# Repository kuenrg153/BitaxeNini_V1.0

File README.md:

# Bitaxe Nini V2.0

Bitaxe Nini is an open-source Bitcoin miner board with **four KF1950 ASICs**. It is a derivative of the
[Bitaxe Gamma Turbo (BitaxeGT)](https://github.com/bitaxeorg/BitaxeGT) and is designed in KiCad 10.

## Features

- 4 x KF1950 ASICs on the bottom side, cooled by a ridged 68 x 68 mm heatsink
- TPS546D24S buck regulator for the ASIC core supply
- ESP32-S3-WROOM-1 controller with USB-C
- 12 V input (screw terminal J1, with an alternate J9 position)
- EMC2101 and EMC2103-2 fan control and temperature monitoring
- 0.91" 128 x 32 I2C OLED module (J4)
- Top-side heat spreading: exposed copper pours and filled thermal vias under a 60 x 44 x 44 mm finned heatsink
  (mounted on electrically insulating thermal tape), plus a 12 x 12 x 5 mm heatsink on the regulator
- 65.1 x 112.1 mm, 4-layer, 2 oz outer copper, ENIG, filled and capped via-in-pad

Firmware: [kuenrg153/ESP-Miner](https://github.com/kuenrg153/ESP-Miner), the ESP-Miner fork for the KF1950.

## Repository layout

| Path | Contents |
|---|---|
| `BitaxeNini_V2.0.kicad_pro` / `.kicad_sch` / `.kicad_pcb` | KiCad project, schematics (ASIC, Power, ESP32, fan sheets) and board |
| `bitaxe.kicad_sym`, `bitaxe.pretty/`, `3d/` | Project library: symbols, footprints and 3D models (bundled, no external library needed) |
| `Manufacturing Files/` | Gerbers, drill files, BOM with DigiKey part numbers, pick-and-place, fab and assembly drawings, `FAB_NOTES.txt` |
| `BitaxeNini_V2.0.step` | Full 3D assembly model |
| `doc/` | Renders |

The project library is referenced through `${KIPRJMOD}`, so the project opens with all footprints and 3D models
straight after cloning.

## Manufacturing

Upload `Manufacturing Files/BitaxeNini_V2.0_MFG_261119.zip` to the board house and include the notes in
`Manufacturing Files/FAB_NOTES.txt`. Key requirements: via-in-pad filled and capped (IPC-4761 Type VII) and the
intentional front solder-mask openings. The KF1950 ASICs are not sold by distributors and are supplied separately.

## License

This project is licensed under the
[CERN Open Hardware Licence Version 2 - Strongly Reciprocal (CERN-OHL-S-2.0)](https://choosealicense.com/licenses/cern-ohl-s-2.0/).
See [LICENSE](LICENSE) for the full text.

## Acknowledgments

- [bitaxeorg/BitaxeGT](https://github.com/bitaxeorg/BitaxeGT), the design this board is derived from
- [esp-miner](https://github.com/bitaxeorg/esp-miner) and the Bitaxe open-source community
- The OLED footprint reference: [MichMich/KiCad-SSD1306_OLED-0.91-128x32](https://github.com/MichMich/KiCad-SSD1306_OLED-0.91-128x32)

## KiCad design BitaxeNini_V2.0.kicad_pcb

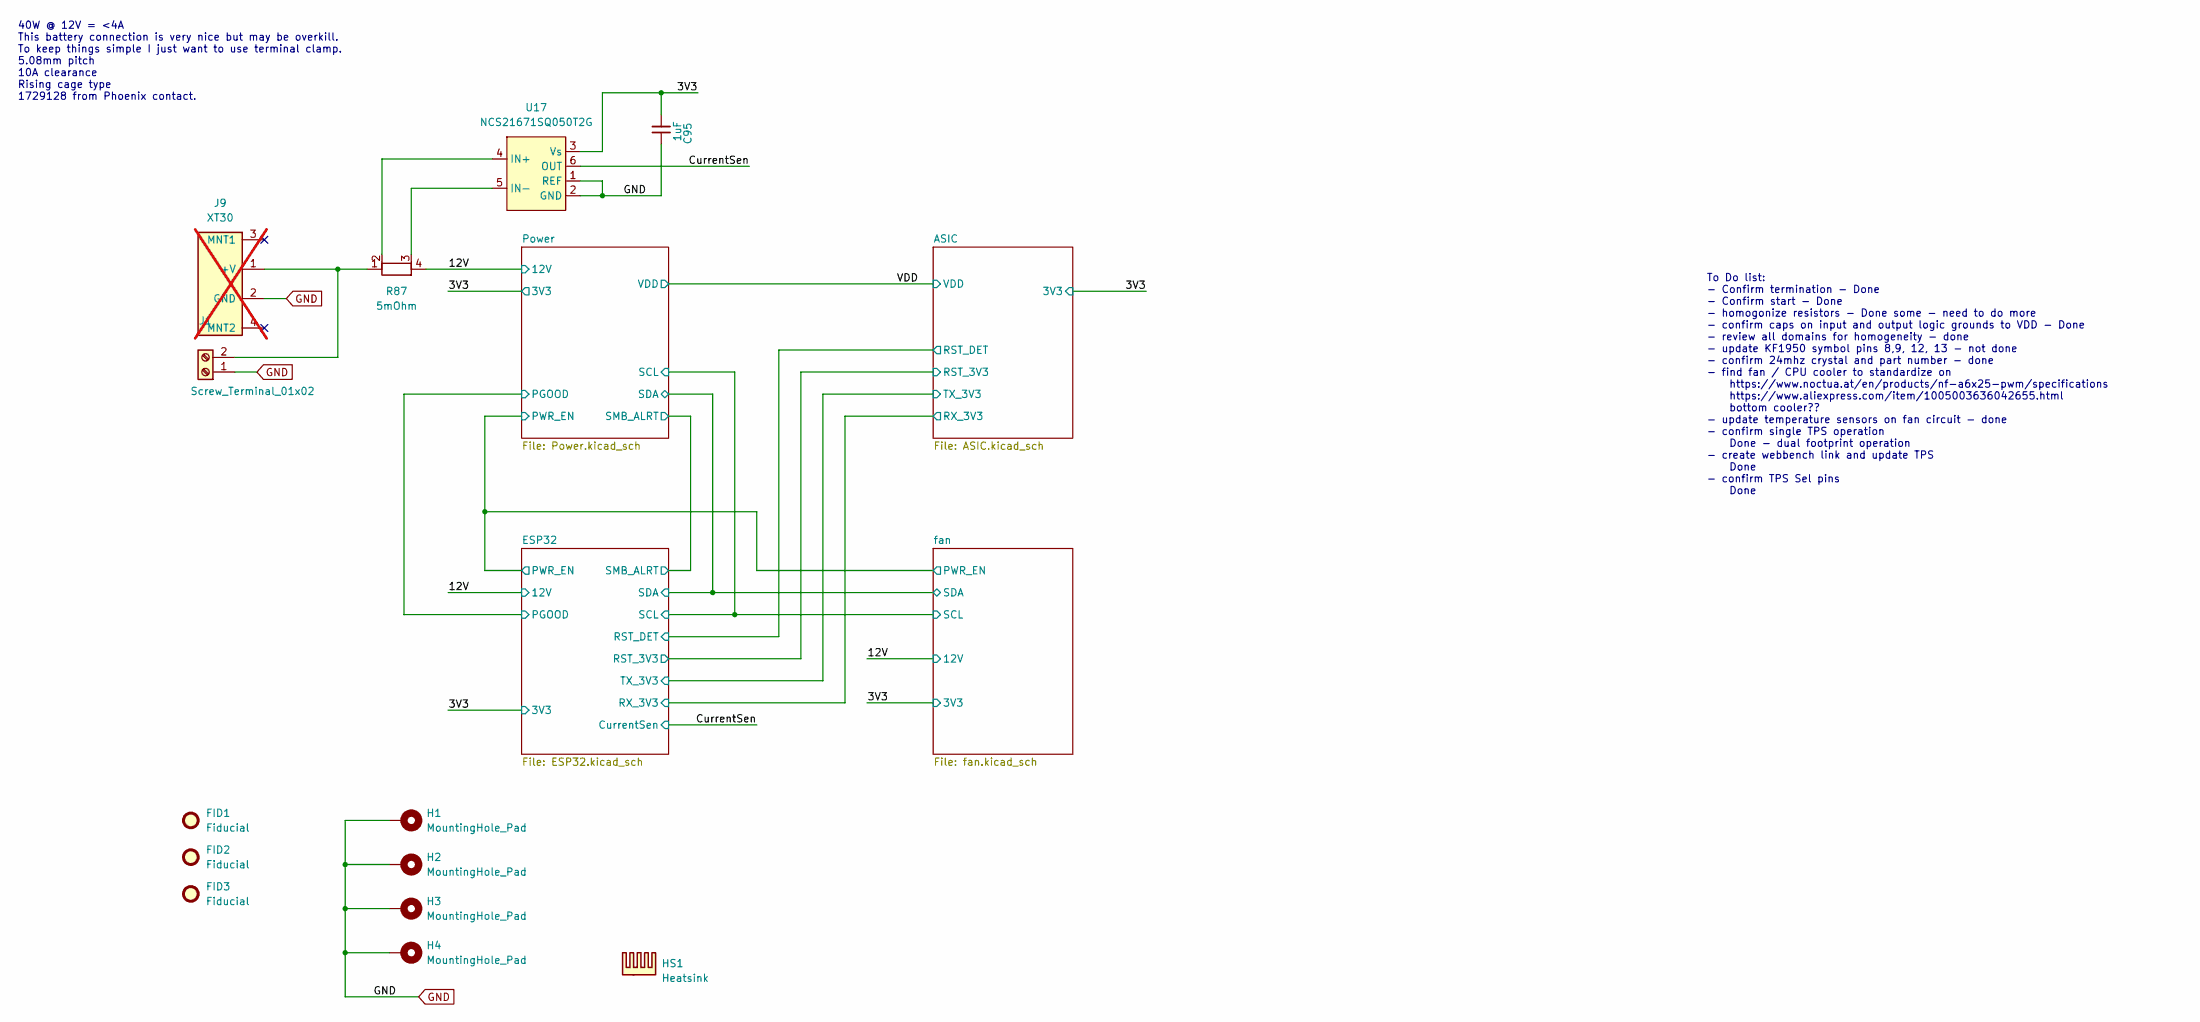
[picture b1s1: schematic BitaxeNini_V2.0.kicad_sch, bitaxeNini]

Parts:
C95: 1uF; C_0402_1005Metric; PARTNO GRM155R61E105KA12D
FID1, FID2, FID3: Fiducial; Fiducial_1mm_Mask2mm
H1, H2, H3, H4: MountingHole_Pad; MountingHole_3.2mm_M3_Pad_Via
HS1: Heatsink; Heatsink-2hole-68mm
J1: Screw_Terminal_01x02; TerminalBlock_Phoenix_MKDS-1,5-2_1x02_P5.00mm_Horizontal; PARTNO 1729128
J9: XT30; XT30PW-M; PARTNO XT30PW-M; not fitted
R87: 5mOhm; R_Shunt_Vishay_WSK2512_6332Metric_T1.19mm; PARTNO WSK25125L000FEA
U17: NCS21671SQ050T2G; SOT-363_SC-70-6; PARTNO NCS21671SQ050T2G

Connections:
/3V3: C95.1, U17.3 (Vs); also elsewhere on the board
/12V: R87.4; also elsewhere on the board
/CurrentSen: U17.6 (OUT); also elsewhere on the board
GND: C95.2, H1.1 (1_1), H2.1 (1_1), H3.1 (1_1), H4.1 (1_1), J1.1, J9.2 (GND), U17.1 (REF), U17.2 (GND); also elsewhere on the board
unnamed: J1.2, J9.1 (+V), R87.1
unnamed: R87.2, U17.4 (IN+)
unnamed: R87.3, U17.5 (IN-)

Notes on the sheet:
40W @ 12V = <4A This battery connection is very nice but may be overkill. To keep things simple I just want to use terminal clamp. 5.08mm pitch 10A clearance Rising cage type 1729128 from Phoenix contact.
To Do list: - Confirm termination - Done - Confirm start - Done - homogonize resistors - Done some - need to do more - confirm caps on input and output logic grounds to VDD - Done - review all domains for homogeneity - done - update KF1950 symbol pins 8,9, 12, 13 - not done - confirm 24mhz crystal 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

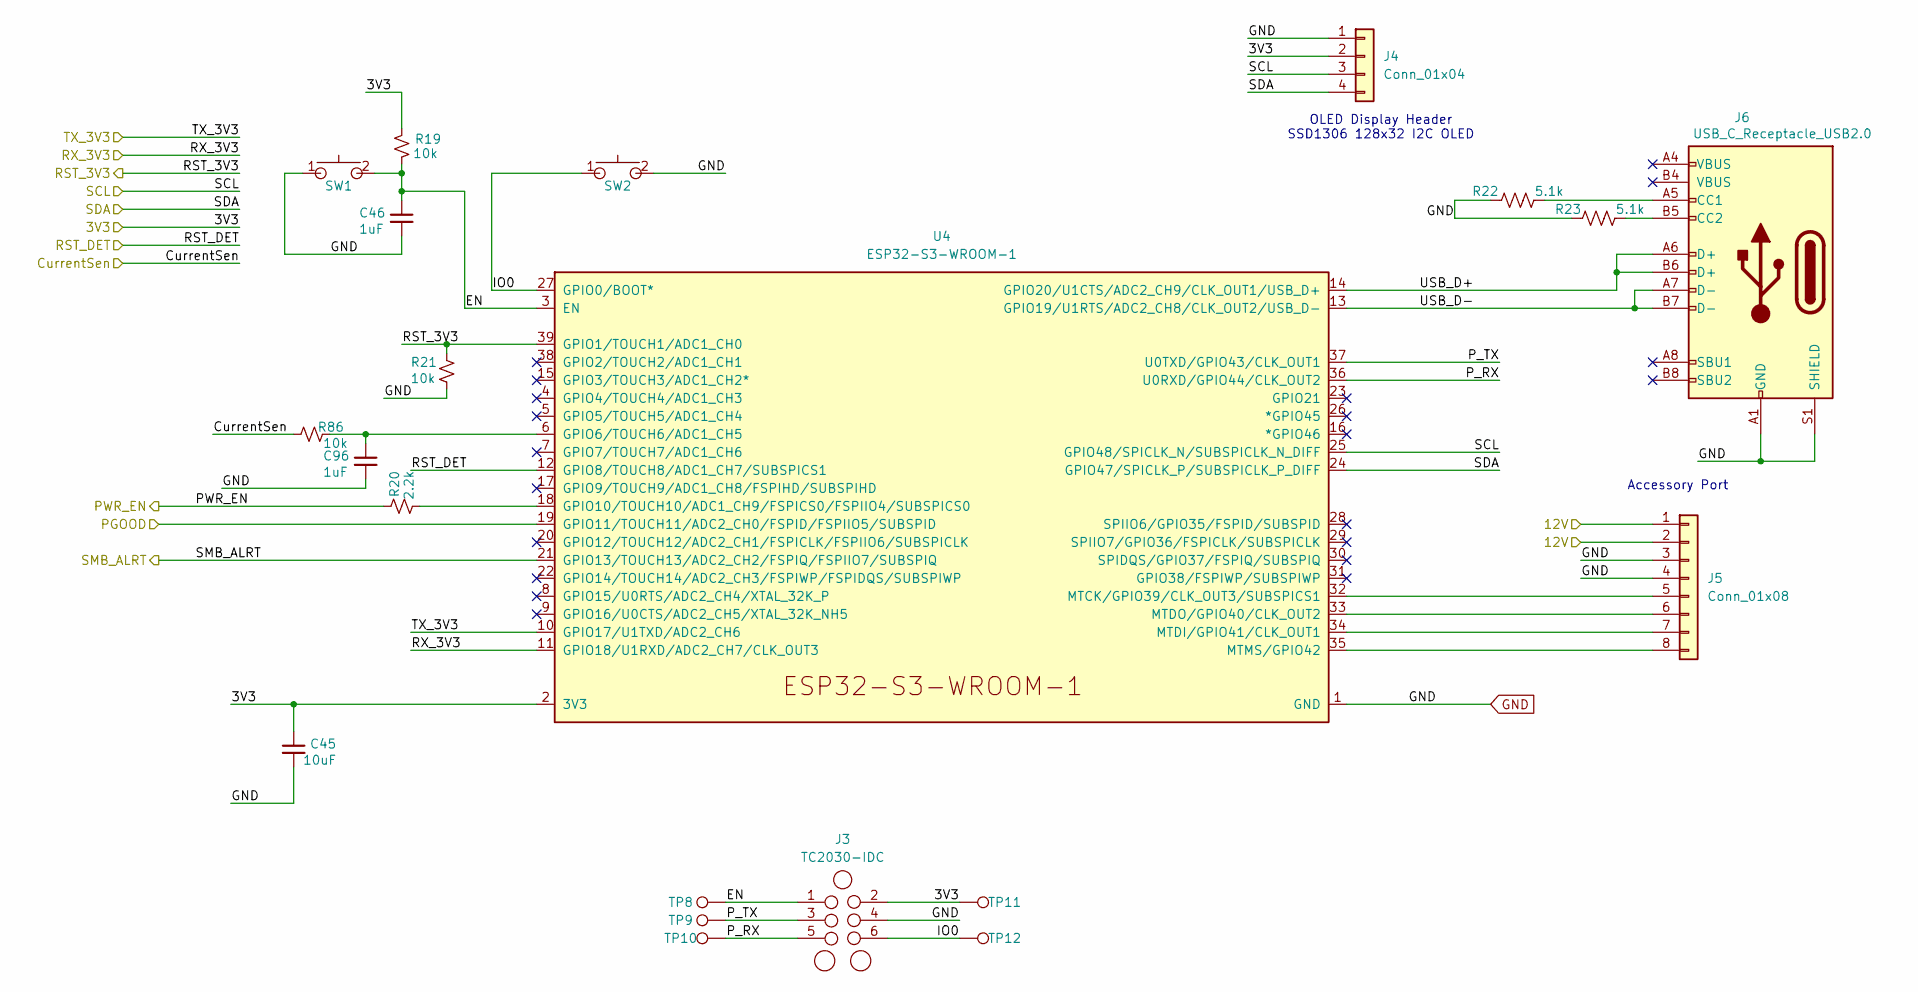
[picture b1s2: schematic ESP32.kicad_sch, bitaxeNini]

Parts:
C45: 10uF; C_0402_1005Metric; Voltage 6.3V; PARTNO GMC04X5R106M6R3NT
C46, C96: 1uF; C_0402_1005Metric; PARTNO GRM155R61E105KA12D
J3: TC2030-IDC; Tag-Connect_TC2030-IDC-NL_2x03_P1.27mm_Vertical
J4: Conn_01x04; OLED_0.91in_128x32_I2C_Module
J5: Conn_01x08; FPC-SMD_P0.50-8P_FGS-XJ-H2.0; PARTNO FFC2B35-08-T; LCSC C262657
J6: USB_C_Receptacle_USB2.0; USB_C_Receptacle_GCT_USB4105-xx-A; PARTNO USB4105-GF-A
R19, R21, R86: 10k; R_0402_1005Metric; PARTNO RC0402FR-0710KL
R20: 2.2k; R_0402_1005Metric; PARTNO RC0402FR-072K2L
R22, R23: 5.1k; R_0402_1005Metric; PARTNO RC0402FR-075K1L
SW1, SW2: SWITCH-SPST; SW_TL3330AF130QG_EWI; PARTNO TL3330AF130QG
TP8: EN; TestPoint_Pad_D1.0mm
TP9: PTX; TestPoint_Pad_D1.0mm
TP10: PRX; TestPoint_Pad_D1.0mm
TP11: 3V3; TestPoint_Pad_D1.0mm
TP12: IO0; TestPoint_Pad_D1.0mm
U4: ESP32-S3-WROOM-1; PARTNO ESP32-S3-WROOM-1-N16R8

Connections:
/3V3: C45.1, J3.2, J4.2, R19.2, TP11.1 (1_1), U4.2 (3V3); also elsewhere on the board
/12V: J5.1, J5.2; also elsewhere on the board
/ASIC/RST_3V3: R21.2, U4.39 (GPIO1/TOUCH1/ADC1_CH0); also elsewhere on the board
/ASIC/RST_DET: U4.12 (GPIO8/TOUCH8/ADC1_CH7/SUBSPICS1); also elsewhere on the board
/ASIC/RX_3V3: U4.11 (GPIO18/U1RXD/ADC2_CH7/CLK_OUT3); also elsewhere on the board
/ASIC/TX_3V3: U4.10 (GPIO17/U1TXD/ADC2_CH6); also elsewhere on the board
/CurrentSen: R86.2; also elsewhere on the board
/ESP32/EN: C46.1, J3.1, R19.1, SW1.2, TP8.1 (1_1), U4.3 (EN)
/ESP32/IO0: J3.6, SW2.1, TP12.1 (1_1), U4.27 (GPIO0/BOOT*)
/ESP32/PWR_EN: R20.2; also elsewhere on the board
/ESP32/P_RX: J3.5, TP10.1 (1_1), U4.36 (U0RXD/GPIO44/CLK_OUT2)
/ESP32/P_TX: J3.3, TP9.1 (1_1), U4.37 (U0TXD/GPIO43/CLK_OUT1)
/ESP32/SCL: J4.3, U4.25 (GPIO48/SPICLK_N/SUBSPICLK_N_DIFF); also elsewhere on the board
/ESP32/SDA: J4.4, U4.24 (GPIO47/SPICLK_P/SUBSPICLK_P_DIFF); also elsewhere on the board
/ESP32/SMB_ALRT: U4.21 (GPIO13/TOUCH13/ADC2_CH2/FSPIQ/FSPIIO7/S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); also elsewhere on the board
/ESP32/USB_D+: J6.A6 (D+), J6.B6 (D+), U4.14 (GPIO20/U1CTS/ADC2_CH9/CLK_OUT1/USB_D+)
/ESP32/USB_D-: J6.A7 (D-), J6.B7 (D-), U4.13 (GPIO19/U1RTS/ADC2_CH8/CLK_OUT2/USB_D-)
/Power/PGOOD: U4.19 (GPIO11/TOUCH11/ADC2_CH0/FSPID/FSPIIO5/S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); also elsewhere on the board
GND: C45.2, C46.2, C96.2, J3.4, J4.1, J5.3, J5.4, J6.A1 (GND), J6.B1 (GND), J6.S1 (SHIELD), R21.1, R22.1, R23.1, SW1.1, SW2.2, U4.1 (GND), U4.40 (GND), U4.41 (GND); also elsewhere on the board
unnamed: J5.5, U4.32 (MTCK/GPIO39/CLK_OUT3/SUBSPICS1)
unnamed: J5.6, U4.33 (MTDO/GPIO40/CLK_OUT2)
unnamed: J5.7, U4.34 (MTDI/GPIO41/CLK_OUT1)
unnamed: J5.8, U4.35 (MTMS/GPIO42)
unnamed: J6.A5 (CC1), R22.2
unnamed: J6.B5 (CC2), R23.2
unnamed: C96.1, R86.1, U4.6 (GPIO6/TOUCH6/ADC1_CH5)
unnamed: R20.1, U4.18 (GPIO10/TOUCH10/ADC1_CH9/FSPICS0/FSPIIO4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)

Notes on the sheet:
OLED Display Header SSD1306 128x32 I2C OLED
Accessory Port

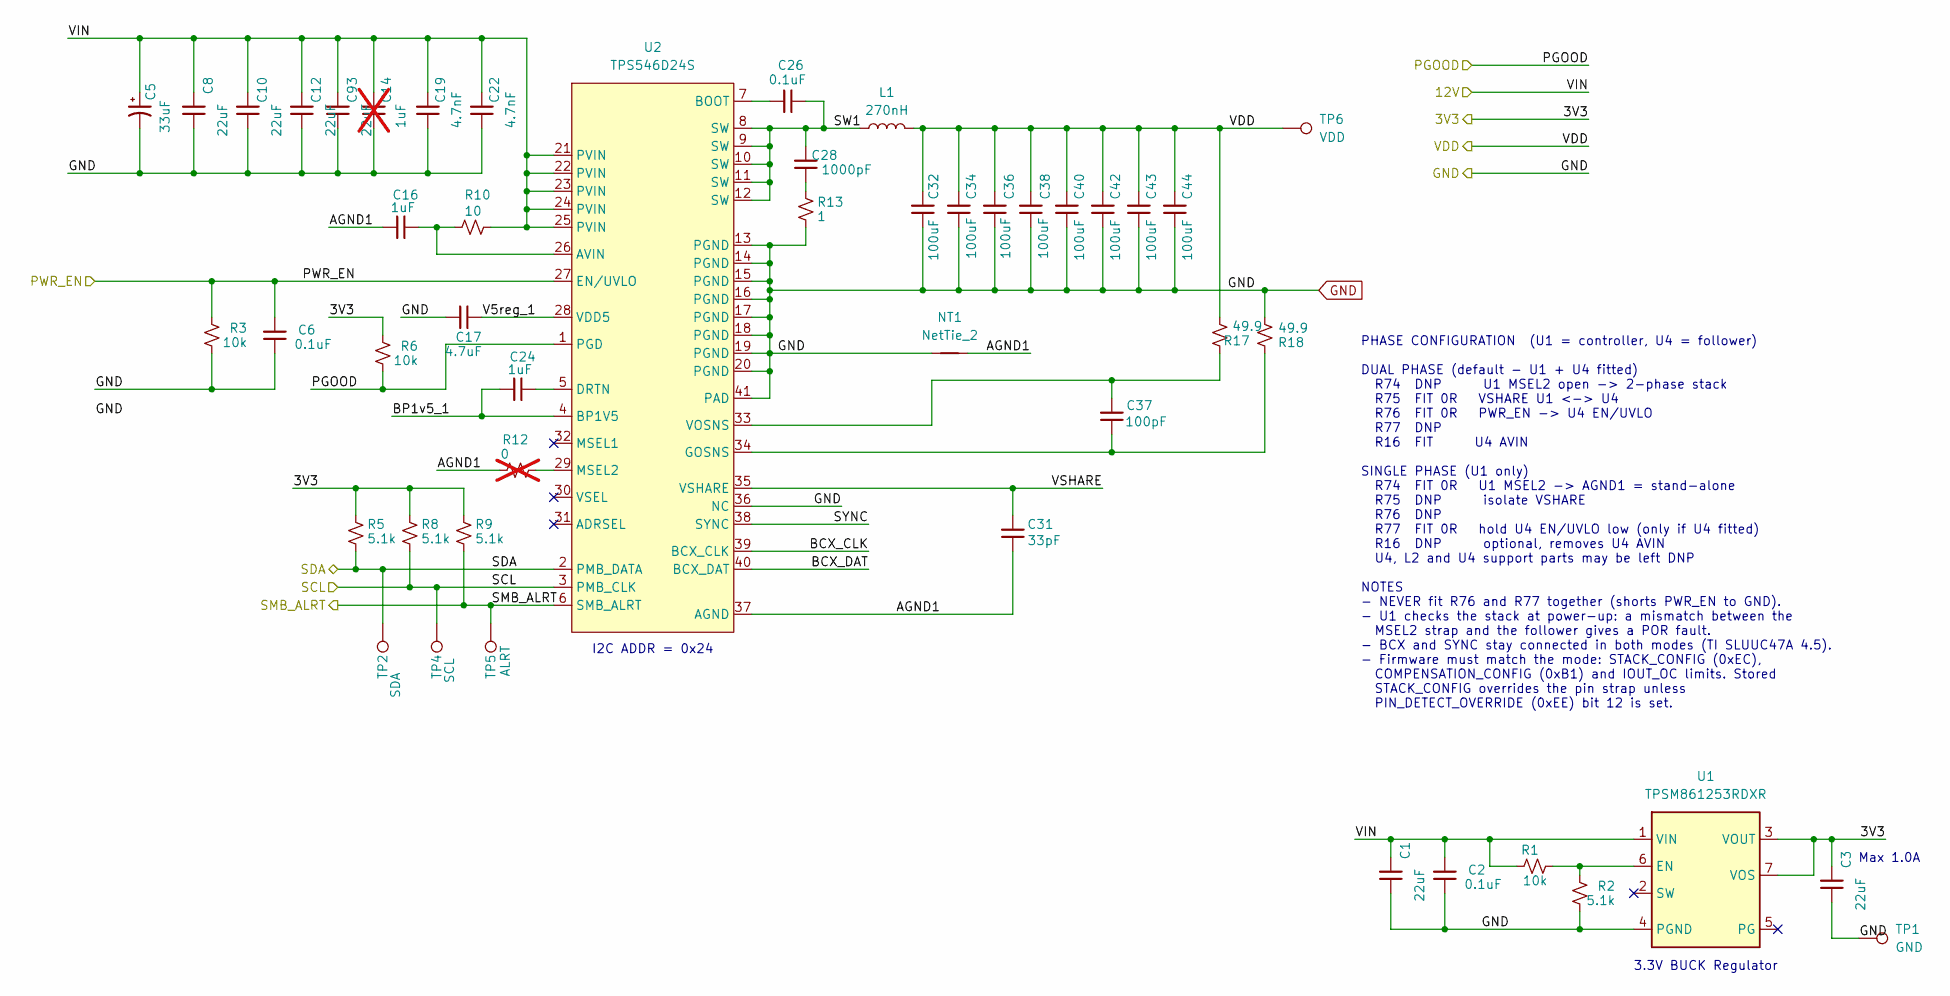
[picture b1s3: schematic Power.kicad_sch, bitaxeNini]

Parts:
C1, C3: 22uF; C_1206_3216Metric; PARTNO CL31A226KAHNNNE
C2, C6, C26: 0.1uF; C_0402_1005Metric; PARTNO GRM155R71E104KE14D
C5: 33uF; CP_EIA-7343-31_Kemet-D; PARTNO T495D336K025ATE300
C8, C10, C12, C93: 22uF; C_1206_3216Metric; Voltage 25V; PARTNO CL31A226KAHNNNE
C14: 1uF; C_0402_1005Metric; PARTNO GRM155R61E105KA12D; not fitted
C16, C24: 1uF; C_0402_1005Metric; PARTNO GRM155R61E105KA12D
C17: 4.7uF; C_0402_1005Metric; PARTNO GRM155R61A475MEAAD
C19, C22: 4.7nF; C_0402_1005Metric; PARTNO GRM155R71E472KA01D
C28: 1000pF; C_0603_1608Metric; Voltage 50V; PARTNO CC0603KRX7R9BB102
C31: 33pF; C_0402_1005Metric; PARTNO KGM05ACG1E330JH
C32, C34, C36, C38, C40, C42, C43, C44: 100uF; C_1206_3216Metric; Voltage 6.3V; PARTNO CL31A107MQHNNNE
C37: 100pF; C_0402_1005Metric; Voltage 50V; PARTNO CC0402JRNPO9BN101
L1: 270nH; SLC1175-271MEC_COC; PARTNO SLC1175-271MEC
NT1: NetTie_2; NetTie-2_SMD_Pad0.2mmx1mm
R1, R3, R6: 10k; R_0402_1005Metric; PARTNO RC0402FR-0710KL
R2, R5, R8, R9: 5.1k; R_0402_1005Metric; PARTNO RC0402FR-075K1L
R10: 10; R_0402_1005Metric; PARTNO RC0402FR-0710RL
R12: 0; R_0402_1005Metric; PARTNO RC0402JR-070RL; not fitted
R13: 1; R_0805_2012Metric; PARTNO ESR10EZPJ1R0
R17, R18: 49.9; R_0603_1608Metric; PARTNO RC0603FR-0749R9L
TP1: GND; TestPoint_Pad_D1.0mm
TP2: SDA; TestPoint_Pad_D1.0mm
TP4: SCL; TestPoint_Pad_D1.0mm
TP5: ALRT; TestPoint_Pad_D1.0mm
TP6: VDD; TestPoint_Pad_D1.0mm
U1: TPSM861253RDXR; TPSM863257RDX; PARTNO TPSM861253RDXR
U2: TPS546D24S; LQFN40-CLIP; PARTNO TPS546D24SRVFR

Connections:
/3V3: C3.1, R5.1, R6.2, R8.1, R9.1, U1.3 (VOUT), U1.7 (VOS); also elsewhere on the board
/12V: C1.1, C2.1, C5.1, C8.1, C10.1, C12.1, C14.1, C19.1, C22.1, C93.1, R1.2, R10.1, U1.1 (VIN), U2.21 (PVIN), U2.22 (PVIN), U2.23 (PVIN), U2.24 (PVIN), U2.25 (PVIN); also elsewhere on the board
/ESP32/PWR_EN: C6.1, R3.2, U2.27 (EN/UVLO); also elsewhere on the board
/ESP32/SCL: R8.2, TP4.1 (1_1), U2.3 (PMB_CLK); also elsewhere on the board
/ESP32/SDA: R5.2, TP2.1 (1_1), U2.2 (PMB_DATA); also elsewhere on the board
/ESP32/SMB_ALRT: R9.2, TP5.1 (1_1), U2.6 (SMB_ALRT); also elsewhere on the board
/Power/AGND1: C16.1, C31.1, NT1.1, R12.2, U2.37 (AGND)
/Power/BCX_CLK: U2.39 (BCX_CLK)
/Power/BCX_DAT: U2.40 (BCX_DAT)
/Power/BP1v5_1: C24.1, U2.4 (BP1V5)
/Power/PGOOD: R6.1, U2.1 (PGD); also elsewhere on the board
/Power/SW1: C26.2, C28.1, L1.1, U2.8 (SW), U2.9 (SW), U2.10 (SW), U2.11 (SW), U2.12 (SW)
/Power/SYNC: U2.38 (SYNC)
/Power/V5reg_1: C17.2, U2.28 (VDD5)
/Power/VSHARE: C31.2, U2.35 (VSHARE)
GND: C1.2, C2.2, C3.2, C5.2, C6.2, C8.2, C10.2, C12.2, C14.2, C17.1, C19.2, C22.2, C32.1, C34.1, C36.1, C38.1, C40.1, C42.1, C43.1, C44.1, C93.2, NT1.2, R2.1, R3.1, R13.2, R18.1, TP1.1 (1_1), U1.4 (PGND), U2.13 (PGND), U2.14 (PGND), U2.15 (PGND), U2.16 (PGND), U2.17 (PGND), U2.18 (PGND), U2.19 (PGND), U2.20 (PGND), U2.36 (NC), U2.41 (PAD); also elsewhere on the board
unnamed: C28.2, R13.1
unnamed: R1.1, R2.2, U1.6 (EN)
unnamed: C16.2, R10.2, U2.26 (AVIN)
unnamed: C26.1, U2.7 (BOOT)
unnamed: C24.2, U2.5 (DRTN)
unnamed: C37.2, R18.2, U2.34 (GOSNS)
unnamed: R12.1, U2.29 (MSEL2)
unnamed: C37.1, R17.1, U2.33 (VOSNS)
VDD: C32.2, C34.2, C36.2, C38.2, C40.2, C42.2, C43.2, C44.2, L1.2, R17.2, TP6.1 (1_1); also elsewhere on the board

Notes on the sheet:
PHASE CONFIGURATION (U1 = controller, U4 = follower) DUAL PHASE (default - U1 + U4 fitted) R74 DNP U1 MSEL2 open -> 2-phase stack R75 FIT 0R VSHARE U1 <-> U4 R76 FIT 0R PWR_EN -> U4 EN/UVLO R77 DNP R16 FIT U4 AVIN SINGLE PHASE (U1 only) R74 FIT 0R U1 MSEL2 -> AGND1 = stand-alone R75 DNP isolate VSH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
3.3V BUCK Regulator
I2C ADDR = 0x24
Max 1.0A

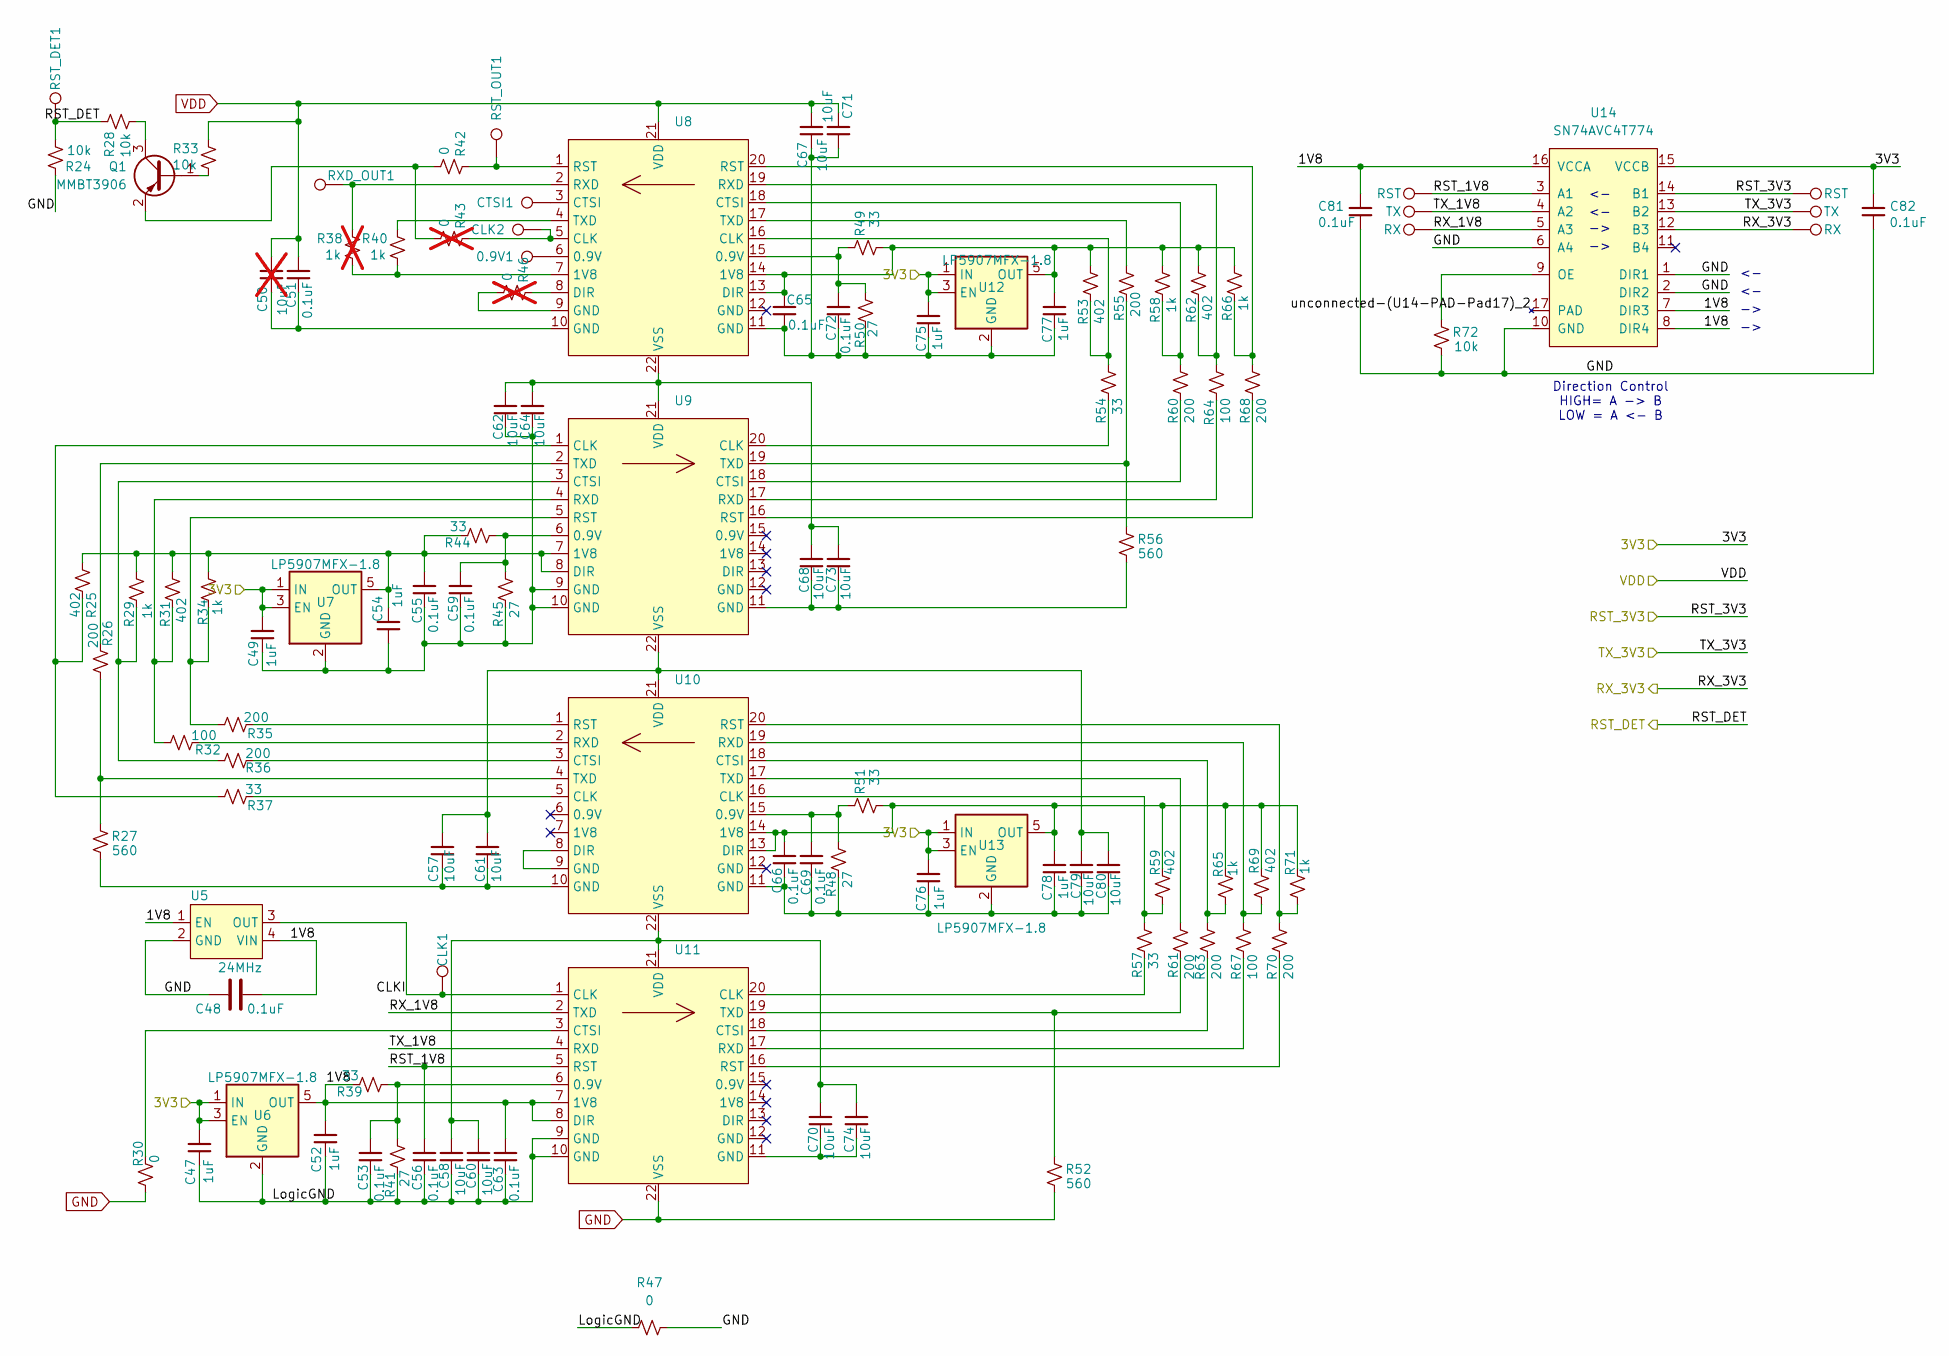
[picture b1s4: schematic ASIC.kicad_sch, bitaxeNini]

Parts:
0.9V1: TestPoint; TestPoint_Pad_D1.0mm
C47, C49, C52, C54, C75, C76, C77, C78: 1uF; C_0402_1005Metric; PARTNO GRM155R61E105KA12D
C48, C51, C53, C55, C56, C59, C63, C65, C66, C69, C72, C81, C82: 0.1uF; C_0402_1005Metric; PARTNO GRM155R71E104KE14D
C50: 10uF; C_0402_1005Metric; PARTNO GMC04X5R106M6R3NT; not fitted
C57, C58, C60, C61, C62, C64, C67, C68, C70, C71, C73, C74, C79, C80: 10uF; C_0402_1005Metric; PARTNO GMC04X5R106M6R3NT
CLK1, CLK2: TestPoint; TestPoint_Pad_D1.0mm
CTSI1: TestPoint; TestPoint_Pad_D1.0mm
Q1: MMBT3906; SOT-23; PARTNO MMBT3906LT1G
R24, R28, R33, R72: 10k; R_0402_1005Metric; PARTNO RC0402FR-0710KL
R25, R31, R53, R59, R62, R69: 402; R_0402_1005Metric; PARTNO RC0402FR-07402RL
R26, R35, R36, R55, R60, R61, R63, R68, R70: 200; R_0402_1005Metric; PARTNO RC0402FR-07200RL
R27, R52, R56: 560; R_0402_1005Metric; PARTNO RC0402FR-07560RL
R29, R34, R40, R58, R65, R66, R71: 1k; R_0402_1005Metric; PARTNO RC0402FR-071KL
R30, R42, R47: 0; R_0402_1005Metric; PARTNO RC0402JR-070RL
R32, R64, R67: 100; R_0402_1005Metric; PARTNO RC0402FR-07100RL
R37, R39, R44, R49, R51, R54, R57: 33; R_0402_1005Metric; PARTNO RC0402FR-0733RL
R38: 1k; R_0402_1005Metric; PARTNO RC0402FR-071KL; not fitted
R41, R45, R48, R50: 27; R_0402_1005Metric; PARTNO RC0402FR-0727RL
R43, R46: 0; R_0402_1005Metric; PARTNO RC0402JR-070RL; not fitted
RST_DET1: TestPoint; TestPoint_Pad_D1.5mm
RST_OUT1: TestPoint; TestPoint_Pad_D1.0mm
RXD_OUT1: TestPoint; TestPoint_Pad_D1.0mm
TP13, TP16: RST; TestPoint_Pad_D1.0mm
TP14, TP17: TX; TestPoint_Pad_D1.0mm
TP15, TP18: RX; TestPoint_Pad_D1.0mm
U5: 24MHz; SMD3225-4P; PARTNO SX3M24.000E20F30THN; LCSC C5137261
U6, U7, U12, U13: LP5907MFX-1.8; SOT-23-5; PARTNO LP5907MFX-1.8/NOPB
U8, U9, U10, U11: KF1950; PARTNO KF1950
U14: SN74AVC4T774; BQB0016A-MFG; PARTNO SN74AXC4T774BQBR

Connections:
/3V3: C47.1, C49.1, C75.1, C76.1, C82.1, U6.1 (IN), U6.3 (EN), U7.1 (IN), U7.3 (EN), U12.1 (IN), U12.3 (EN), U13.1 (IN), U13.3 (EN), U14.15 (VCCB); also elsewhere on the board
/ASIC/1V8: C48.2, C52.1, C63.1, C81.1, R39.1, U5.1 (EN), U5.4 (VIN), U6.5 (OUT), U11.7 (1V8), U11.8 (DIR), U14.7 (DIR3), U14.8 (DIR4), U14.16 (VCCA)
/ASIC/CLKI: CLK1.1 (1_1), U5.3 (OUT), U11.1 (CLK)
/ASIC/LogicGND: C47.2, C52.2, C53.2, C56.2, C58.2, C60.2, C63.2, R41.1, R47.1, U6.2 (GND), U11.9 (GND), U11.10 (GND)
/ASIC/RST_1V8: C56.1, TP13.1 (1_1), U11.5 (RST), U14.3 (A1)
/ASIC/RST_3V3: TP16.1 (1_1), U14.14 (B1); also elsewhere on the board
/ASIC/RST_DET: R24.1, R28.2, RST_DET1.1 (1_1); also elsewhere on the board
/ASIC/RX_1V8: TP15.1 (1_1), U11.2 (TXD), U14.5 (A3)
/ASIC/RX_3V3: TP18.1 (1_1), U14.12 (B3); also elsewhere on the board
/ASIC/TX_1V8: TP14.1 (1_1), U11.4 (RXD), U14.4 (A2)
/ASIC/TX_3V3: TP17.1 (1_1), U14.13 (B2); also elsewhere on the board
GND: C48.1, C81.2, C82.2, R24.2, R30.2, R47.2, R52.1, R72.1, U5.2 (GND), U11.22 (VSS), U14.1 (DIR1), U14.2 (DIR2), U14.6 (A4), U14.10 (GND); also elsewhere on the board
unnamed: 0.9V1.1 (1_1), U8.6 (0.9V)
unnamed: C50.2, C51.1, U8.10 (GND)
unnamed: C53.1, R39.2, R41.2, U11.6 (0.9V)
unnamed: C57.1, C61.1, R27.1, U10.10 (GND)
unnamed: C59.1, R44.2, R45.2, U9.6 (0.9V)
unnamed: C68.2, C73.2, R56.1, U9.11 (GND)
unnamed: C69.1, R48.2, R51.2, U10.15 (0.9V)
unnamed: C70.2, C74.2, U11.11 (GND)
unnamed: C72.1, R49.2, R50.2, U8.15 (0.9V)
unnamed: CLK2.1 (1_1), R43.2, U8.5 (CLK)
unnamed: CTSI1.1 (1_1), U8.3 (CTSI)
unnamed: Q1.1 (B), R33.1
unnamed: Q1.3 (C), R28.1
unnamed: Q1.2 (E), R42.1, R43.1
unnamed: R25.1, R37.2, U9.1 (CLK)
unnamed: R26.1, U9.2 (TXD)
unnamed: R26.2, R27.2, U10.4 (TXD)
unnamed: R29.1, R36.2, U9.3 (CTSI)
unnamed: R30.1, U11.3 (CTSI)
unnamed: R31.1, R32.2, U9.4 (RXD)
unnamed: R32.1, U10.2 (RXD)
unnamed: R34.1, R35.2, U9.5 (RST)
unnamed: R35.1, U10.1 (RST)
unnamed: R36.1, U10.3 (CTSI)
unnamed: R37.1, U10.5 (CLK)
unnamed: R38.1, R40.1, U8.7 (1V8)
unnamed: R38.2, RXD_OUT1.1 (1_1), U8.2 (RXD)
unnamed: R40.2, U8.4 (TXD)
unnamed: R42.2, RST_OUT1.1 (1_1), U8.1 (RST)
unnamed: R46.1, U8.9 (GND)
unnamed: R46.2, U8.8 (DIR)
unnamed: R52.2, R61.1, U11.19 (TXD)
unnamed: R53.1, R54.2, U8.16 (CLK)
unnamed: R54.1, U9.20 (CLK)
unnamed: R55.1, R56.2, U9.19 (TXD)
unnamed: R55.2, U8.17 (TXD)
unnamed: R57.1, U11.20 (CLK)
unnamed: R57.2, R59.1, U10.16 (CLK)
unnamed: R58.1, R60.2, U8.18 (CTSI)
unnamed: R60.1, U9.18 (CTSI)
unnamed: R61.2, U10.17 (TXD)
unnamed: R62.1, R64.2, U8.19 (RXD)
unnamed: R63.1, U11.18 (CTSI)
unnamed: R63.2, R65.1, U10.18 (CTSI)
unnamed: R64.1, U9.17 (RXD)
unnamed: R66.1, R68.2, U8.20 (RST)
unnamed: R67.1, U11.17 (RXD)
unnamed: R67.2, R69.1, U10.19 (RXD)
unnamed: R68.1, U9.16 (RST)
unnamed: R70.1, U11.16 (RST)
unnamed: R70.2, R71.1, U10.20 (RST)
unnamed: C49.2, C54.2, C55.2, C59.2, C62.2, C64.2, R45.1, U7.2 (GND), U9.9 (GND), U9.10 (GND)
unnamed: C54.1, C55.1, R25.2, R29.2, R31.2, R34.2, R44.1, U7.5 (OUT), U9.7 (1V8), U9.8 (DIR)
unnamed: C62.1, C64.1, C68.1, C73.1, U8.22 (VSS), U9.21 (VDD)
unnamed: U10.8 (DIR), U10.9 (GND)
unnamed: C57.2, C61.2, C79.1, C80.1, U9.22 (VSS), U10.21 (VDD)
unnamed: C58.1, C60.1, C70.1, C74.1, U10.22 (VSS), U11.21 (VDD)
unnamed: C65.2, C67.2, C71.1, C72.2, C75.2, C77.2, R50.1, U8.11 (GND), U12.2 (GND)
unnamed: C65.1, C77.1, R49.1, R53.2, R58.2, R62.2, R66.2, U8.13 (DIR), U8.14 (1V8), U12.5 (OUT)
unnamed: C66.2, C69.2, C76.2, C78.2, C79.2, C80.2, R48.1, U10.11 (GND), U13.2 (GND)
unnamed: C66.1, C78.1, R51.1, R59.2, R65.2, R69.2, R71.2, U10.13 (DIR), U10.14 (1V8), U13.5 (OUT)
unnamed: R72.2, U14.9 (OE)
VDD: C50.1, C51.2, C67.1, C71.2, R33.2, U8.21 (VDD); also elsewhere on the board

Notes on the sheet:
Direction Control HIGH= A -> B LOW = A <- B

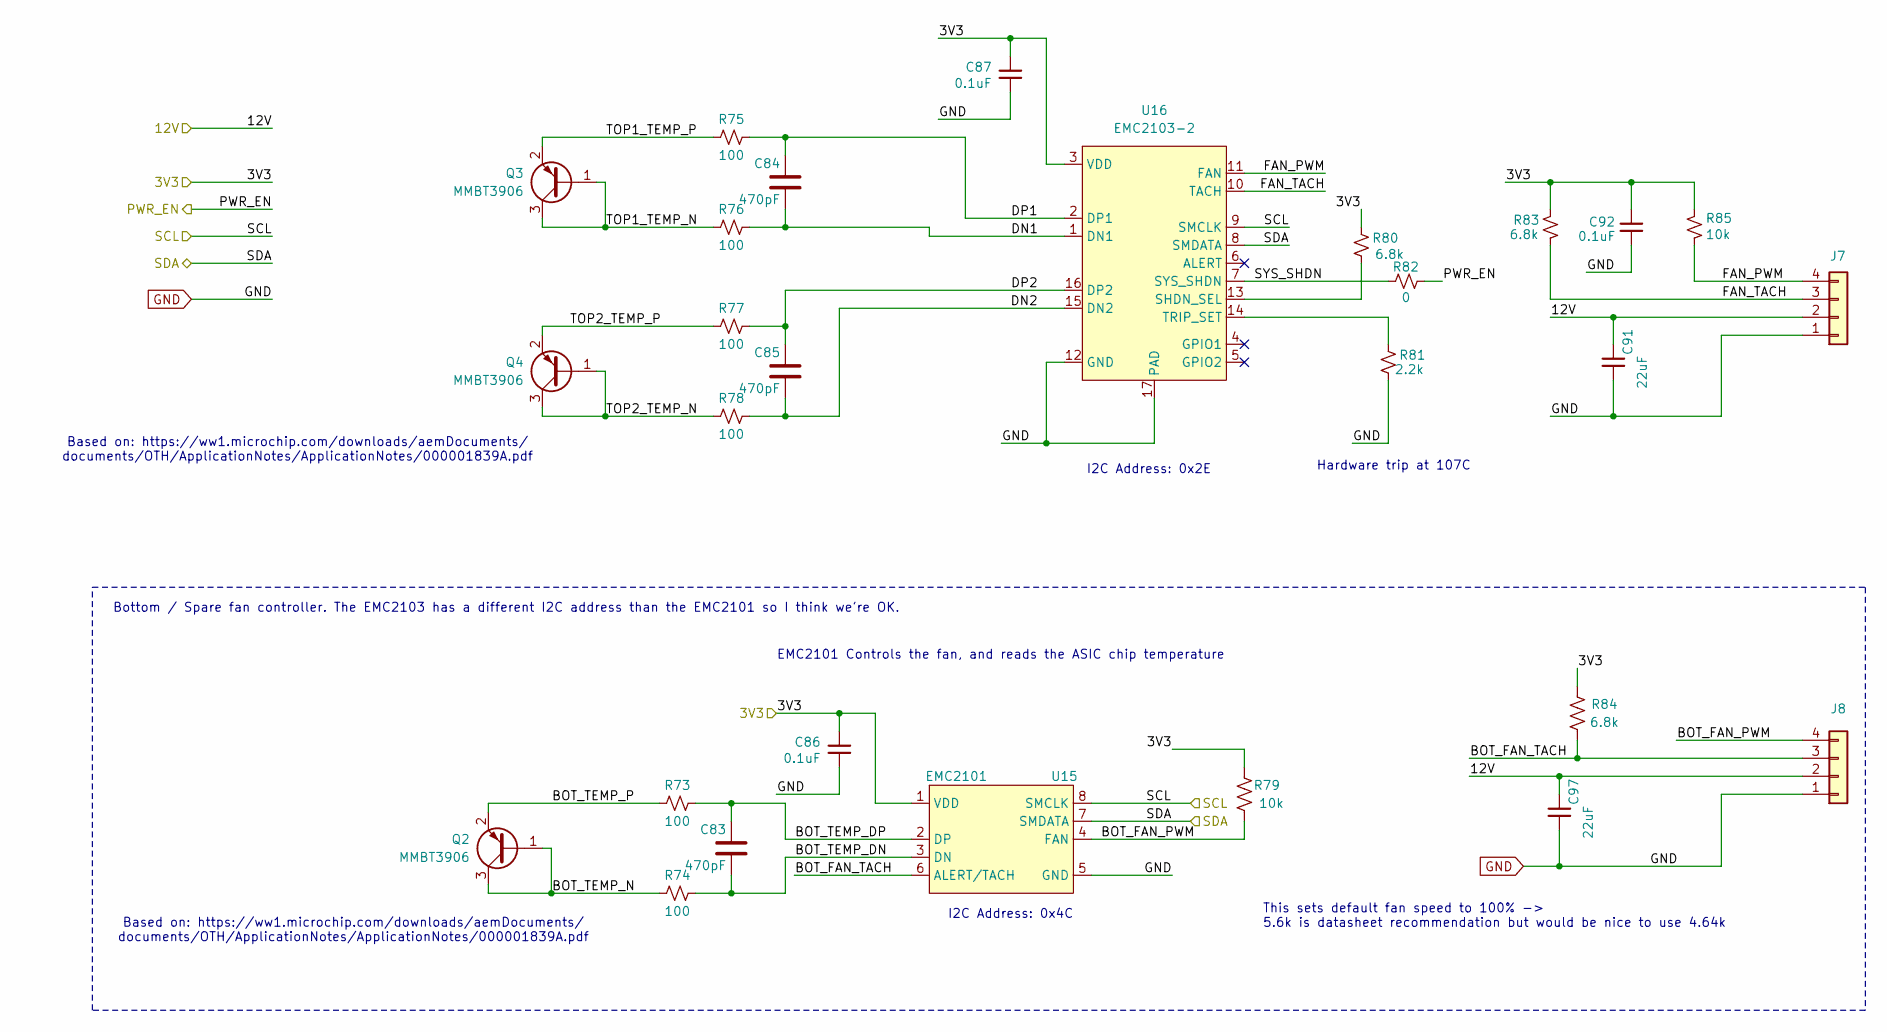
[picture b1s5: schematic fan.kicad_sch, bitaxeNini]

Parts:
C83, C84, C85: 470pF; C_0402_1005Metric; PARTNO CC0402KRX7R9BB471
C86, C87, C92: 0.1uF; C_0402_1005Metric; PARTNO GRM155R71E104KE14D
C91, C97: 22uF; C_1206_3216Metric; PARTNO CL31A226KAHNNNE
J7, J8: Conn_01x04; PinHeader_1x04_P2.54mm_Vertical; PARTNO 0470531000
Q2, Q3, Q4: MMBT3906; SOT-23; PARTNO MMBT3906LT1G
R73, R74, R75, R76, R77, R78: 100; R_0402_1005Metric; PARTNO RC0402FR-07100RL
R79, R85: 10k; R_0402_1005Metric; PARTNO RC0402FR-0710KL
R80, R83, R84: 6.8k; R_0402_1005Metric; PARTNO RC0402FR-076K8L
R81: 2.2k; R_0402_1005Metric; PARTNO RC0402FR-072K2L
R82: 0; R_0402_1005Metric; PARTNO RC0402JR-070RL
U15: EMC2101; TSSOP-8_3x3mm_P0.65mm; PARTNO EMC2101-R-ACZL-TR
U16: EMC2103-2; QFN-16-1EP_4x4mm_P0.65mm_EP2.1x2.1mm; PARTNO EMC2103-2-AP-TR

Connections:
/3V3: C86.1, C87.1, C92.1, R79.2, R80.2, R83.2, R84.2, R85.2, U15.1 (VDD), U16.3 (VDD); also elsewhere on the board
/12V: C91.1, C97.1, J7.2, J8.2; also elsewhere on the board
/ESP32/PWR_EN: R82.1; also elsewhere on the board
/ESP32/SCL: U15.8 (SMCLK), U16.9 (SMCLK); also elsewhere on the board
/ESP32/SDA: U15.7 (SMDATA), U16.8 (SMDATA); also elsewhere on the board
/fan/BOT_FAN_PWM: J8.4, R79.1, U15.4 (FAN)
/fan/BOT_FAN_TACH: J8.3, R84.1, U15.6 (ALERT/TACH)
/fan/BOT_TEMP_DN: C83.2, R74.1, U15.3 (DN)
/fan/BOT_TEMP_DP: C83.1, R73.2, U15.2 (DP)
/fan/BOT_TEMP_N: Q2.1 (B), Q2.3 (C), R74.2
/fan/BOT_TEMP_P: Q2.2 (E), R73.1
/fan/DN1: C84.2, R76.1, U16.1 (DN1)
/fan/DN2: C85.2, R78.1, U16.15 (DN2)
/fan/DP1: C84.1, R75.2, U16.2 (DP1)
/fan/DP2: C85.1, R77.2, U16.16 (DP2)
/fan/FAN_PWM: J7.4, R85.1, U16.11 (FAN)
/fan/FAN_TACH: J7.3, R83.1, U16.10 (TACH)
/fan/SYS_SHDN: R82.2, U16.7 (SYS_SHDN)
/fan/TOP1_TEMP_N: Q3.1 (B), Q3.3 (C), R76.2
/fan/TOP1_TEMP_P: Q3.2 (E), R75.1
/fan/TOP2_TEMP_N: Q4.1 (B), Q4.3 (C), R78.2
/fan/TOP2_TEMP_P: Q4.2 (E), R77.1
GND: C86.2, C87.2, C91.2, C92.2, C97.2, J7.1, J8.1, R81.1, U15.5 (GND), U16.12 (GND), U16.17 (PAD); also elsewhere on the board
unnamed: R80.1, U16.13 (SHDN_SEL)
unnamed: R81.2, U16.14 (TRIP_SET)

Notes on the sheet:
Based on: https://ww1.microchip.com/downloads/aemDocuments/ documents/OTH/ApplicationNotes/ApplicationNotes/000001839A.pdf
I2C Address: 0x4C
I2C Address: 0x2E
Bottom / Spare fan controller. The EMC2103 has a different I2C address than the EMC2101 so I think we're OK.
Hardware trip at 107C
This sets default fan speed to 100% -> 5.6k is datasheet recommendation but would be nice to use 4.64k
EMC2101 Controls the fan, and reads the ASIC chip temperature
